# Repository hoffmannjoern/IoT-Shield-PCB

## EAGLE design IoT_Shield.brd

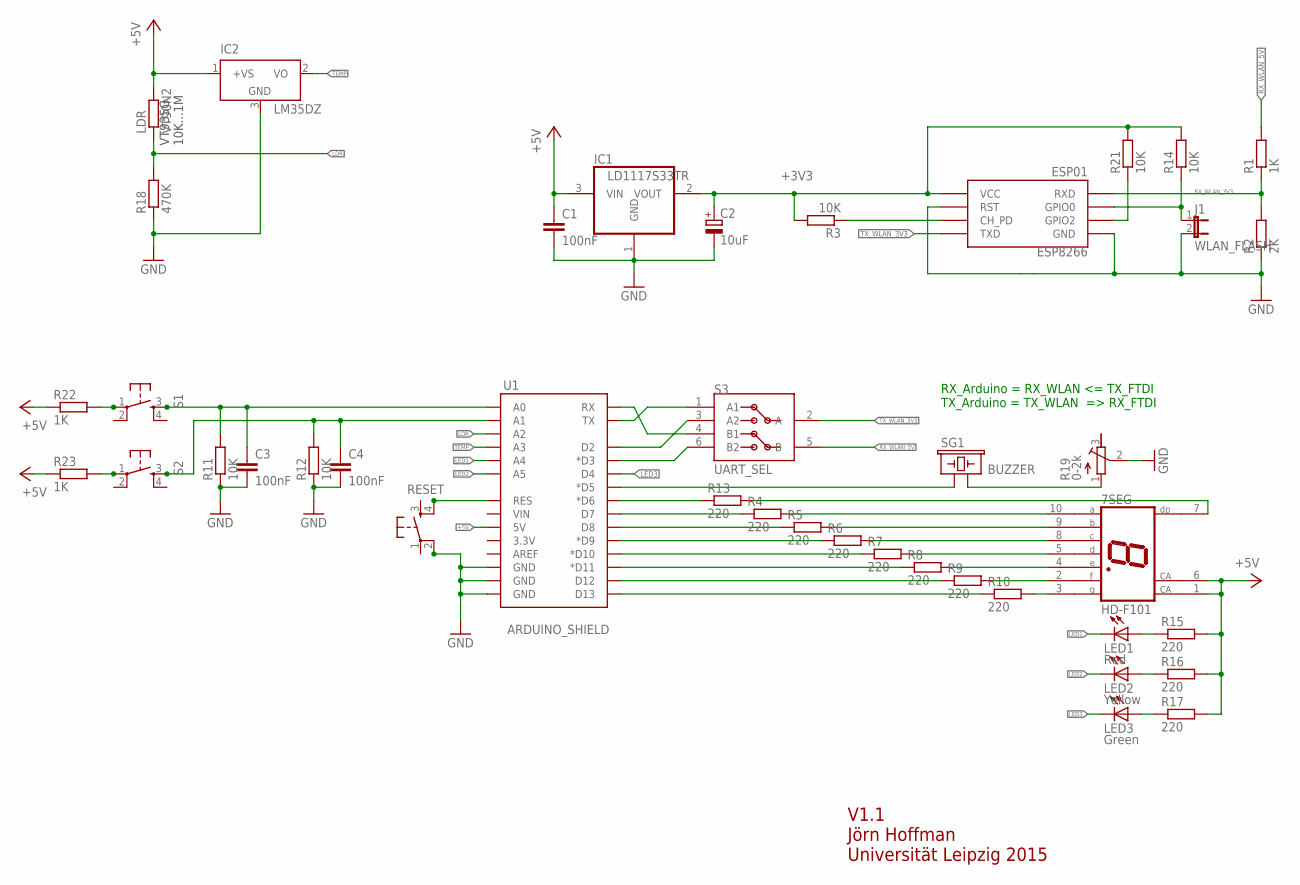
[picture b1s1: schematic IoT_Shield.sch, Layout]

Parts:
7SEG: HD-F101; HDSP-E
C1, C3, C4: 100nF; C0805
C2: 10uF; A/3216-18R
ESP8266: ESP01
IC1: LD1117S33TR; SOT223
IC2: LM35DZ; TO92
J1: WLAN_FLASH; JP1
LDR: VT90N2; 0204V
LED1: Red; LED5MM
LED2: Yellow; LED5MM
LED3: Green; LED5MM
R1, R22, R23: 1K; R0805
R2: 2K; R0805
R3, R11, R12, R14, R21: 10K; R0805
R4, R5, R6, R7, R8, R9, R10, R13, R15, R16, R17: 220; R0805
R18: 470K; R0805
R19: 0-2k; RTRIM4G/J
RESET: TAC_SWITCHSMD; DTSM-6
S1, S2: TAC_SWITCHSMD; DTSM-6
S3: UART_SEL; SMD
SG1: BUZZER; BUZZER-12MM
U1: ARDUINO_SHIELD; DUEMILANOVE_VIAS

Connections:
+3V3: C2.+, ESP8266.VCC, IC1.2 (VOUT), R3.2, R14.2, R21.2
+5V: 7SEG.1 (CA), 7SEG.6 (CA), C1.1, IC1.3 (VIN), IC2.1 (+VS), LDR.2, R15.2, R16.2, R17.2, R22.1, R23.1, U1.5V
GND: C1.2, C2.-, C3.2, C4.2, ESP8266.GND, ESP8266.RST, IC1.1 (GND), IC2.3 (GND), J1.2, R2.1, R11.1, R12.1, R18.1, R19.2 (S), RESET.2, U1.GND@0 (GND), U1.GND@1 (GND), U1.GND@2 (GND)
LDR: LDR.1, R18.2, U1.A2
LED1: LED1.K (C), U1.A4
LED2: LED2.K (C), U1.A5
LED3: LED3.K (C), U1.D4
unnamed: ESP8266.CH_PD, R3.1
unnamed: R4.1, U1.D7
unnamed: R5.1, U1.D8
unnamed: R6.1, U1.D9 (*D9)
unnamed: R7.1, U1.D10 (*D10)
unnamed: R8.1, U1.D11 (*D11)
unnamed: R9.1, U1.D12
unnamed: R10.1, U1.D13
unnamed: 7SEG.10 (A), R4.2
unnamed: 7SEG.9 (B), R5.2
unnamed: 7SEG.8 (C), R6.2
unnamed: 7SEG.5 (D), R7.2
unnamed: 7SEG.4 (E), R8.2
unnamed: 7SEG.2 (F), R9.2
unnamed: 7SEG.3 (G), R10.2
unnamed: SG1.+ (1), U1.D5 (*D5)
unnamed: C3.1, R11.2, S1.3, U1.A0
unnamed: C4.1, R12.2, S2.3, U1.A1
unnamed: 7SEG.7 (DP), R13.2
unnamed: R13.1, U1.D6 (*D6)
unnamed: S3.4 (B1), U1.RX
unnamed: S3.3 (A2), U1.D2
unnamed: S3.1 (A1), U1.TX
unnamed: S3.6 (B2), U1.D3 (*D3)
unnamed: ESP8266.GPIO0, J1.1, R14.1
unnamed: LED1.A, R15.1
unnamed: LED2.A, R16.1
unnamed: LED3.A, R17.1
unnamed: RESET.4, U1.RES
unnamed: ESP8266.GPIO2, R21.1
unnamed: R22.2, S1.1
unnamed: R23.2, S2.1
unnamed: R19.1 (A), SG1.- (2)
RX_WLAN_3V3: ESP8266.RX (RXD), R1.1, R2.2
RX_WLAN_5V: R1.2, S3.5 (B)
TEMP: IC2.2 (VO), U1.A3
TX_WLAN_3V3: ESP8266.TX (TXD), S3.2 (A)

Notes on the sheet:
V1.1 Jörn Hoffman Universität Leipzig 2015
VT935G 10K...1M
RX_Arduino = RX_WLAN <= TX_FTDI TX_Arduino = TX_WLAN => RX_FTDI

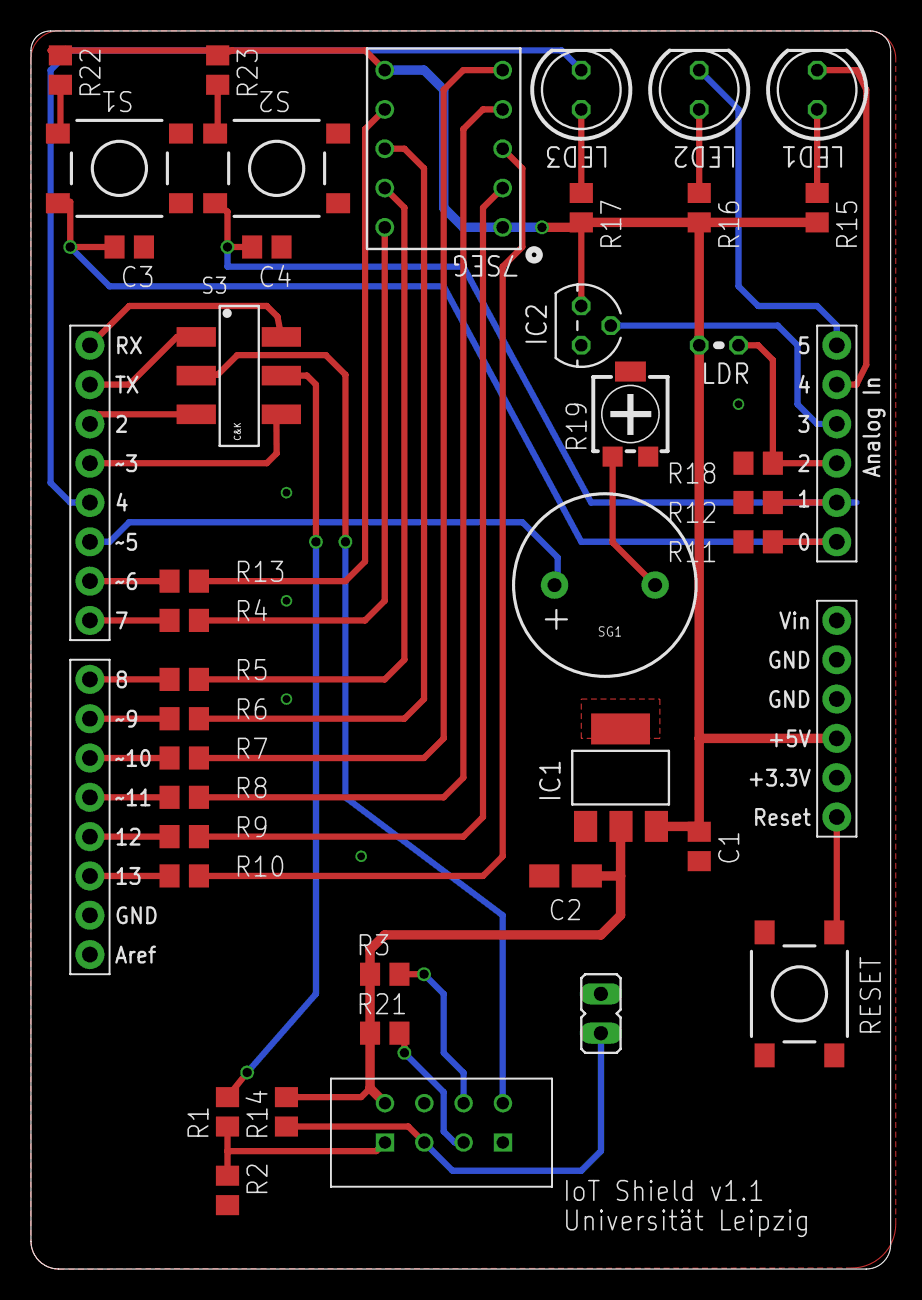
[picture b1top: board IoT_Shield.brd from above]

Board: 2 copper layers, 55.5 x 80.0 mm, 41 parts (0 on the bottom side), 44 nets.

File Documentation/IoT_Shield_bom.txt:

Stückliste exportiert aus /Users/joern/Documents/eagle/IoT_Shield/IoT_Shield.sch am 24.08.15 13:06

Part    Value          Device                Package          Description                                       MF MPN     OC_FARNELL OC_NEWARK
7SEG    HD-F101        HD-F101               HDSP-E           LED DISPLAY                                                  unknown    unknown  
C1      100nF          C-EUC0805             C0805            CAPACITOR, European symbol                                                       
C2      10uF           CPOL-EUA/3216-18R     A/3216-18R       POLARIZED CAPACITOR, European symbol                                             
C3      100nF          C-EUC0805             C0805            CAPACITOR, European symbol                                                       
C4      100nF          C-EUC0805             C0805            CAPACITOR, European symbol                                                       
ESP8266 ESP01          ESP01                 ESP01            ESP8266 Wifi module 01                                       unknown             
IC1     LD1117S33TR    REG1117               SOT223           800mA and 1A Low Dropout (LDO) Positive Regulator    REG1117 1097566    14P6981  
IC2     LM35DZ         LM35CZ                TO92             Single-Supply Centigrade Temperature Sensor                                      
J1      WLAN_FLASH     JP1E                  JP1              JUMPER                                                                           
LDR     VT90N2         R-EU_0204/2V          0204V            RESISTOR, European symbol                                                        
LED1    Red            LED5MM                LED5MM           LED                                                                              
LED2    Yellow         LED5MM                LED5MM           LED                                                                              
LED3    Green          LED5MM                LED5MM           LED                                                                              
R1      1K             R-EU_R0805            R0805            RESISTOR, European symbol                                                        
R2      2K             R-EU_R0805            R0805            RESISTOR, European symbol                                                        
R3      10K            R-EU_R0805            R0805            RESISTOR, European symbol                                                        
R4      220            R-EU_R0805            R0805            RESISTOR, European symbol                                                        
R5      220            R-EU_R0805            R0805            RESISTOR, European symbol                                                        
R6      220            R-EU_R0805            R0805            RESISTOR, European symbol                                                        
R7      220            R-EU_R0805            R0805            RESISTOR, European symbol                                                        
R8      220            R-EU_R0805            R0805            RESISTOR, European symbol                                                        
R9      220            R-EU_R0805            R0805            RESISTOR, European symbol                                                        
R10     220            R-EU_R0805            R0805            RESISTOR, European symbol                                                        
R11     10K            R-EU_R0805            R0805            RESISTOR, European symbol                                                        
R12     10K            R-EU_R0805            R0805            RESISTOR, European symbol                                                        
R13     220            R-EU_R0805            R0805            RESISTOR, European symbol                                                        
R14     10K            R-EU_R0805            R0805            RESISTOR, European symbol                                                        
R15     220            R-EU_R0805            R0805            RESISTOR, European symbol                                                        
R16     220            R-EU_R0805            R0805            RESISTOR, European symbol                                                        
R17     220            R-EU_R0805            R0805            RESISTOR, European symbol                                                        
R18     470K           R-EU_R0805            R0805            RESISTOR, European symbol                                                        
R19     0-2k           R-TRIMM4G/J           RTRIM4G/J        Trimm resistor                                                                   
R21     10K            R-EU_R0805            R0805            RESISTOR, European symbol                                                        
R22     1K             R-EU_R0805            R0805            RESISTOR, European symbol                                                        
R23     1K             R-EU_R0805            R0805            RESISTOR, European symbol                                                        
RESET   TAC_SWITCHSMD  DTSM-6                DTSM-6                                                                                            
S1      TAC_SWITCHSMD  DTSM-6                DTSM-6                                                                                            
S2      TAC_SWITCHSMD  DTSM-6                DTSM-6                                                                                            
S3      UART_SEL       JS202011SCQN          SMD                                                                                               
SG1     BUZZER         BUZZERPTH             BUZZER-12MM      Buzzer 12mm                                                                      
U1      ARDUINO_SHIELD ARDUINO_SHIELDNO_SILK DUEMILANOVE_VIAS Arduino shield footprint                                     unknown

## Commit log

2015-08-24 Initial commit
    - All assets are tested
    IoT Shield v1.1:
    - add Eagle schematic and routed board
    - add documentation and pictures under Documentation/
    - add used and modified Eagle libraries under lib/
    - add specs of the components under Spec/
2015-08-24 Modify gitignore
2015-08-24 Rotate document
    - rotate schematic view form landscape to portrait

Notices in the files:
parts and their libraries:
SparkFun-Boards: Licensing: Creative Commons ShareAlike 4.0 International - https://creativecommons.org/licenses/by-sa/4.0
